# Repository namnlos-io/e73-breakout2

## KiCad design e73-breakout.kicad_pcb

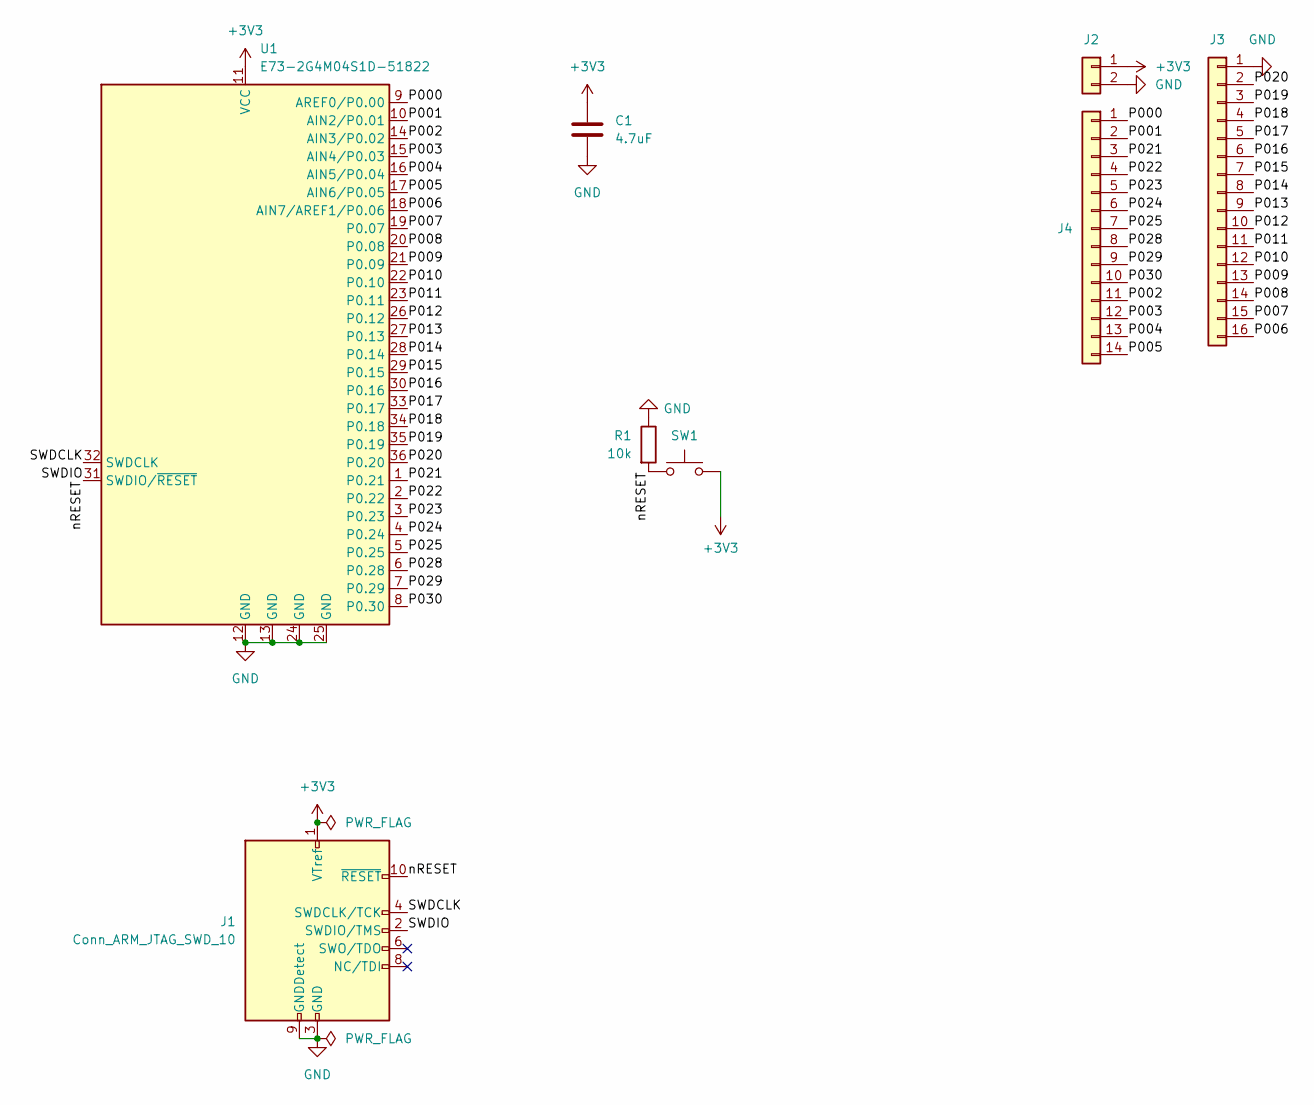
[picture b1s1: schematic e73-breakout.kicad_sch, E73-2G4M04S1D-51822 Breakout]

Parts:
C1: 4.7uF; C_Disc_D3.0mm_W1.6mm_P2.50mm
J1: Conn_ARM_JTAG_SWD_10; PinHeader_2x05_P1.27mm_Vertical
J2: Pin; PinHeader_1x02_P2.54mm_Vertical
J3: Pin; PinHeader_1x16_P2.54mm_Vertical
J4: Pin; PinHeader_1x14_P2.54mm_Vertical
R1: 10k; R_Axial_DIN0204_L3.6mm_D1.6mm_P5.08mm_Horizontal
SW1: 2x3mm; ResetSW_1side
U1: E73-2G4M04S1D-51822; E73-2G4M04S1D

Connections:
+3V3: C1.1, J1.1 (VTref), J2.1, SW1.2, U1.11 (VCC)
/P000: J4.1, U1.9 (AREF0/P0.00)
/P001: J4.2, U1.10 (AIN2/P0.01)
/P002: J4.11, U1.14 (AIN3/P0.02)
/P003: J4.12, U1.15 (AIN4/P0.03)
/P004: J4.13, U1.16 (AIN5/P0.04)
/P005: J4.14, U1.17 (AIN6/P0.05)
/P006: J3.16, U1.18 (AIN7/AREF1/P0.06)
/P007: J3.15, U1.19 (P0.07)
/P008: J3.14, U1.20 (P0.08)
/P009: J3.13, U1.21 (P0.09)
/P010: J3.12, U1.22 (P0.10)
/P011: J3.11, U1.23 (P0.11)
/P012: J3.10, U1.26 (P0.12)
/P013: J3.9, U1.27 (P0.13)
/P014: J3.8, U1.28 (P0.14)
/P015: J3.7, U1.29 (P0.15)
/P016: J3.6, U1.30 (P0.16)
/P017: J3.5, U1.33 (P0.17)
/P018: J3.4, U1.34 (P0.18)
/P019: J3.3, U1.35 (P0.19)
/P020: J3.2, U1.36 (P0.20)
/P021: J4.3, U1.1 (P0.21)
/P022: J4.4, U1.2 (P0.22)
/P023: J4.5, U1.3 (P0.23)
/P024: J4.6, U1.4 (P0.24)
/P025: J4.7, U1.5 (P0.25)
/P028: J4.8, U1.6 (P0.28)
/P029: J4.9, U1.7 (P0.29)
/P030: J4.10, U1.8 (P0.30)
/SWDCLK: J1.4 (SWDCLK/TCK), U1.32 (SWDCLK)
/SWDIO: J1.2 (SWDIO/TMS), J1.10 (~RESET), R1.2, SW1.1, U1.31 (SWDIO/~RESET)
GND: C1.2, J1.3 (GND), J1.5 (GND), J1.9 (GNDDetect), J2.2, J3.1, R1.1, U1.12 (GND), U1.13 (GND), U1.24 (GND), U1.25 (GND)

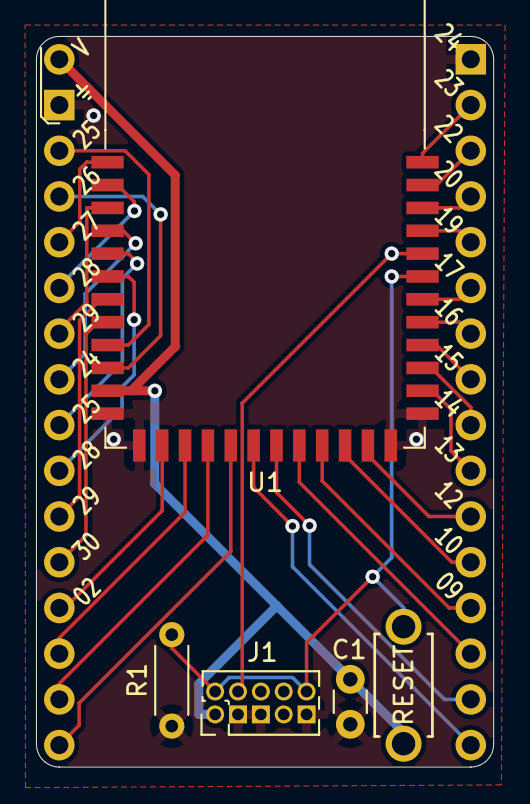
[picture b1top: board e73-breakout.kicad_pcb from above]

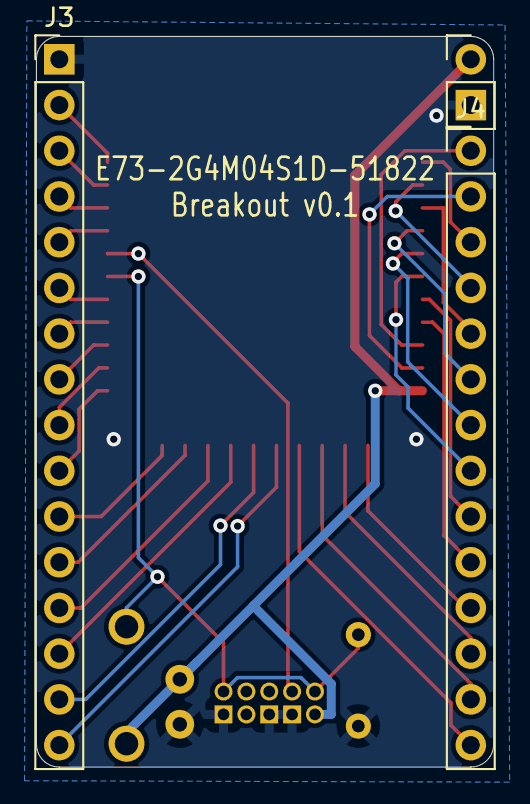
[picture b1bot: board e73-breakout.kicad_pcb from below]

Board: 2 copper layers, 25.4 x 40.6 mm, 8 parts (3 on the bottom side), 33 nets.

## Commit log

2019-03-29 Basic functionality
2019-03-29 layout
2019-03-29 symbols
2019-03-29 Move switch off reset, add silk rev
2019-03-29 not actually D compatible; generate gerbers
2023-06-24 Forking the original repo to make a D compatible breakout.
2023-06-24 Some updates and pictures.
